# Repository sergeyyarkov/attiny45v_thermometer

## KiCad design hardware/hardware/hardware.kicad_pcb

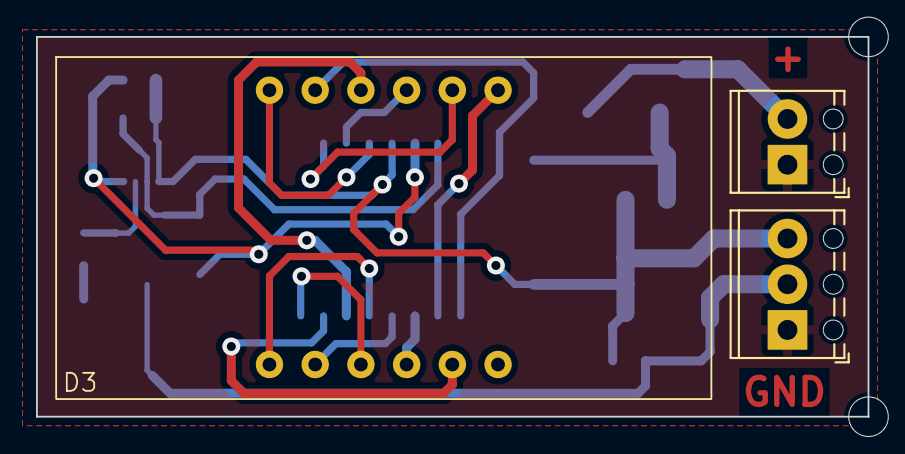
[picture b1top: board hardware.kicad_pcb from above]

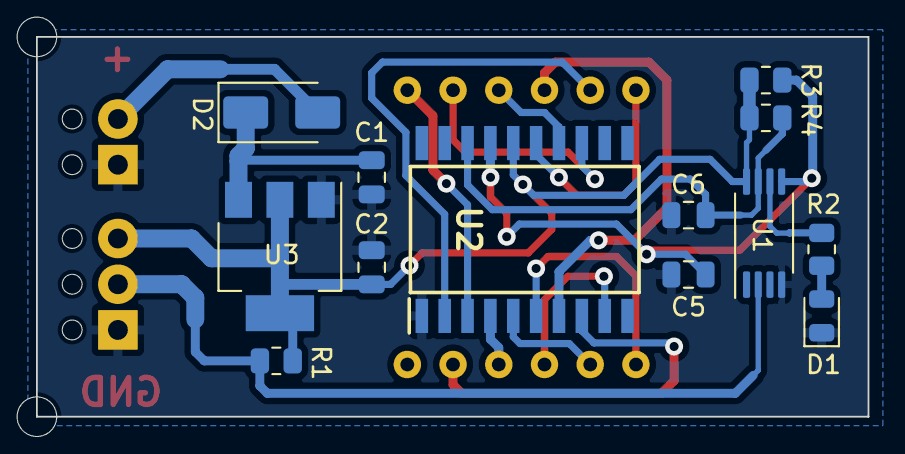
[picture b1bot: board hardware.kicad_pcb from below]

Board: 2 copper layers, 46.2 x 21.1 mm, 16 parts (13 on the bottom side), 20 nets.

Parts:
C1, C2: 10uF; C_0805_2012Metric
C5, C6: 100pF; C_0805_2012Metric
D1: ERR; LED_0805_2012Metric
D2: D_Schottky; D_SMA
D3: 5631BS
J1: SENSOR; TerminalBlock_Phoenix_MPT-0,5-3-2.54_1x03_P2.54mm_Horizontal
J2: POWER; TerminalBlock_Phoenix_MPT-0,5-2-2.54_1x02_P2.54mm_Horizontal
R1: 4.7K; R_0805_2012Metric
R2: 330; R_0805_2012Metric
R3, R4: 10K; R_0805_2012Metric
U1: ATtiny45V; TSSOP-8_4.4x3mm_P0.65mm
U2: TM1637; SOIC127P1045X280-20N
U3: AMS1117-5.0; SOT-223-3_TabPin2

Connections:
+5V: C2.1, J1.3, R1.2, R3.1, R4.1, U1.8 (VCC), U2.16 (VDD), U3.2 (VO)
+12V: C1.1, D2.1 (K), U3.3 (VI)
/CA1: D3.12 (CA1), U2.15 (GRID1)
/CA2: D3.9 (CA2), U2.14 (GRID2)
/CA3: D3.8 (CA3), U2.13 (GRID3)
GND: C1.2, C2.2, C5.2, C6.2, D1.1 (K), J1.1, J2.1, U1.4 (GND), U2.1 (GND), U3.1 (GND)
unnamed: D1.2 (A), R2.2
unnamed: D2.2 (A), J2.2
unnamed: D3.3 (DPX), U2.9 (SEG8/KS8)
unnamed: D3.11 (a), U2.2 (SEG1/KS1)
unnamed: D3.7 (b), U2.3 (SEG2/KS2)
unnamed: D3.4 (c), U2.4 (SEG3/KS3)
unnamed: D3.2 (d), U2.5 (SEG4/KS4)
unnamed: D3.1 (e), U2.6 (SEG5/KS5)
unnamed: D3.10 (f), U2.7 (SEG6/KS6)
unnamed: D3.5 (g), U2.8 (SEG7/KS7)
unnamed: J1.2, R1.1, U1.2 (XTAL1/PB3)
unnamed: C5.1, R3.2, U1.5 (AREF/PB0), U2.17 (DIO)
unnamed: R2.1, U1.6 (PB1)
unnamed: C6.1, R4.2, U1.7 (PB2), U2.18 (CLK)

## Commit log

2023-07-08 read temperature
2023-07-11 ds18b20 lib
2023-08-03 display temp
2023-08-04 Dupd
2023-08-05 select resolution
2023-08-05 show negative numbers
2023-08-05 error handling
2023-08-06 hide zeros & small fix
2023-08-06 watchdog timer
2023-08-06 folder structure
2023-08-07 error handler
2023-08-07 refactor
2023-08-08 schematic
